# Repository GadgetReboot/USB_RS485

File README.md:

# USB_RS485
USB to RS485 Adapter

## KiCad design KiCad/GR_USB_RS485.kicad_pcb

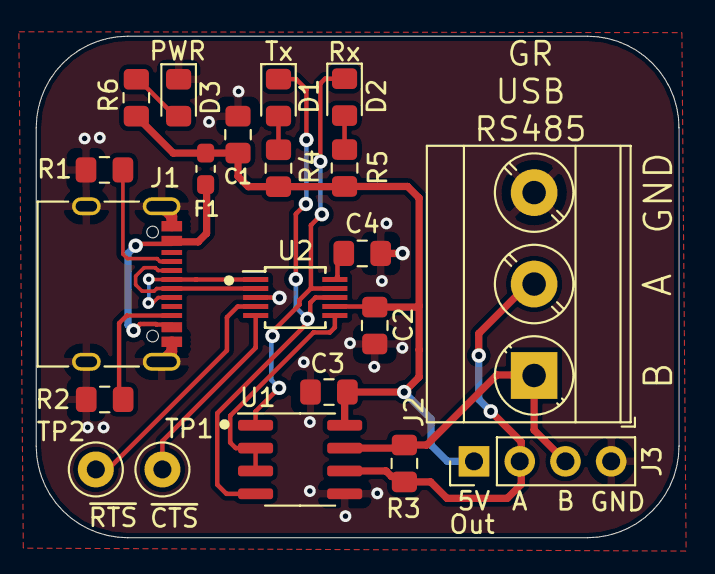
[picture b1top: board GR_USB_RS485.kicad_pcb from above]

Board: 2 copper layers, 35.7 x 27.9 mm, 21 parts (0 on the bottom side), 18 nets.

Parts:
C1: 1uF; C_0805_2012Metric_Pad1.15x1.40mm_HandSolder
C2, C3, C4: 100nF; C_0805_2012Metric_Pad1.15x1.40mm_HandSolder
D1: Rx; LED_0805_2012Metric_Pad1.15x1.40mm_HandSolder
D2: Tx; LED_0805_2012Metric_Pad1.15x1.40mm_HandSolder
D3: Power; LED_0805_2012Metric_Pad1.15x1.40mm_HandSolder
F1: MF-FSMF050X; R_0603_1608Metric_Pad1.05x0.95mm_HandSolder
J1: USB_C_Receptacle; USB_C_Receptacle_XKB_U262-16XN-4BVC11
J2: Screw_Terminal_01x03; TerminalBlock_Phoenix_MKDS-3-3-5.08_1x03_P5.08mm_Horizontal
J3: Conn_01x04; PinHeader_1x04_P2.54mm_Vertical
R1, R2: 5K1; R_0805_2012Metric_Pad1.15x1.40mm_HandSolder
R3: 120r; R_0805_2012Metric_Pad1.15x1.40mm_HandSolder
R4, R5, R6: 2K; R_0805_2012Metric_Pad1.15x1.40mm_HandSolder
TP1, TP2: TestPoint; TestPoint_Loop_D1.80mm_Drill1.0mm_Beaded
U1: MAX485ESA; SOIC-8_3.9x4.9mm_P1.27mm
U2: CH340E; MSOP-10_3x3mm_P0.5mm

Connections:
/485A: J2.2, J3.2, R3.2, U1.6
/485B: J2.1, J3.3, R3.1, U1.7
/D+: J1.A6, J1.B6, U2.1
/D-: J1.A7, J1.B7, U2.2
GNDREF: C1.2, C2.2, C3.2, C4.2, D3.1, J1.A1, J1.A12, J1.B1, J1.B12, J1.S1, J2.3, J3.4, R1.1, R2.1, U1.5, U2.3
unnamed: C4.1, U2.10
unnamed: D1.1, U1.4, U2.8
unnamed: D1.2, R4.1
unnamed: D2.1, U1.1, U2.9
unnamed: D2.2, R5.1
unnamed: D3.2, R6.2
unnamed: F1.1, J1.A4, J1.A9, J1.B4, J1.B9
unnamed: J1.A5, R1.2
unnamed: J1.B5, R2.2
unnamed: TP1.1, U2.5
unnamed: TP2.1, U2.4
unnamed: U1.2, U1.3, U2.6
VCC: C1.1, C2.1, C3.1, F1.2, J3.1, R4.2, R5.2, R6.1, U1.8, U2.7
